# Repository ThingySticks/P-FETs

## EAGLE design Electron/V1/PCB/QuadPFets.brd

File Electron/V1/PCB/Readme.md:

FETish On A Stick
=================

Quat P Channel FETs on a Stick.

All FET's PWM-able (see notes)

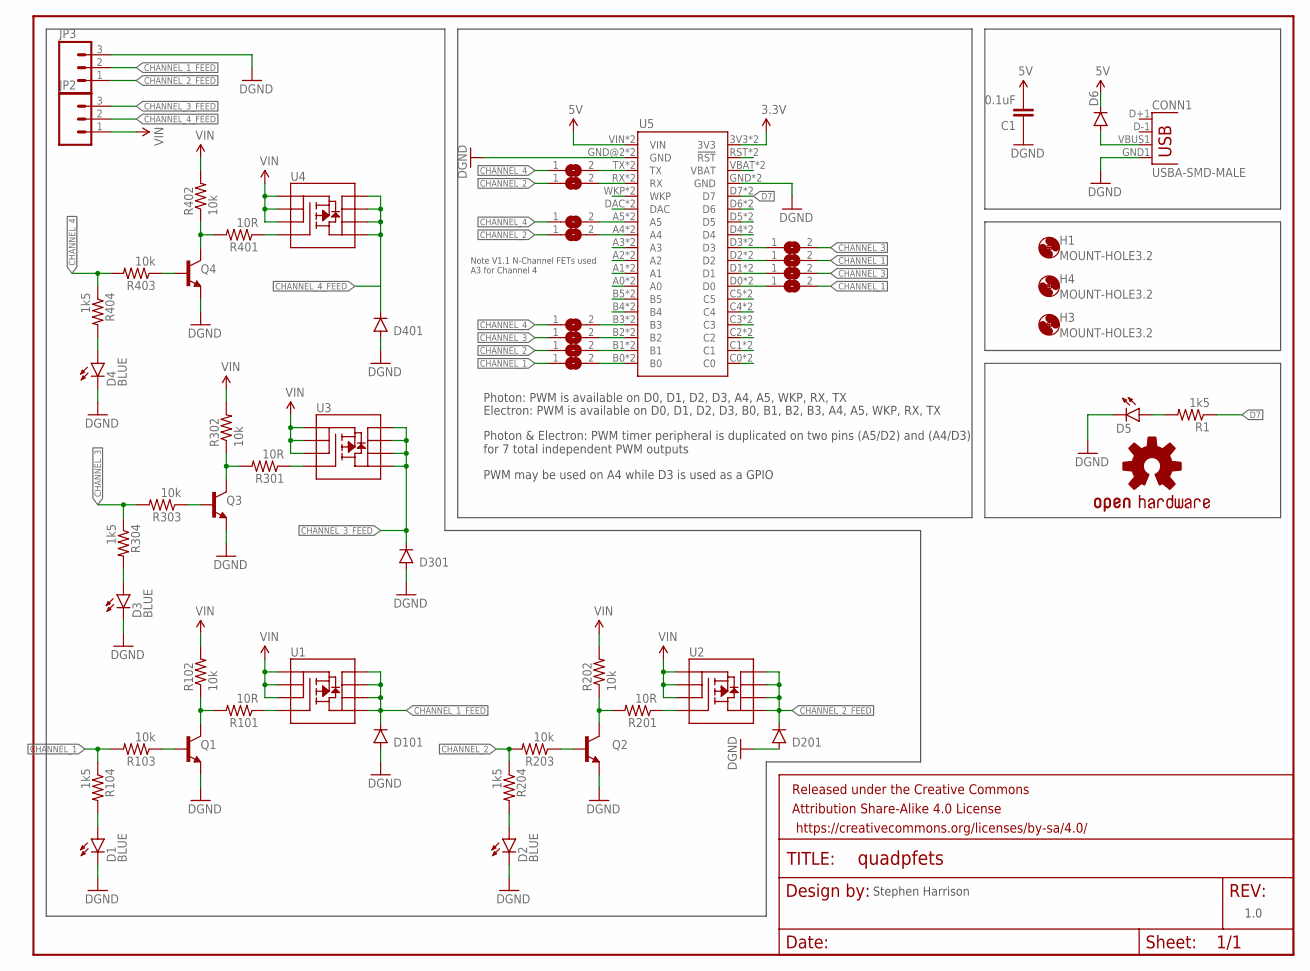
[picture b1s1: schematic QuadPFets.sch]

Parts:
C1: 0.1uF; 0805
CONN1: USBA-SMD-MALE; USB-A-SMT-MALE
D1, D2, D3, D4: BLUE; LED-1206
D5: LED1206-BOTTOM; LED-1206-BOTTOM
D6: DIODESMA; SMA-DIODE
D101, D201, D301, D401: DIODESOD123; SOD-123
FRAME2: FRAME-LETTER; CREATIVE_COMMONS
H1, H3, H4: MOUNT-HOLE3.2; 3,2
JP2, JP3: M03-SCREW-5MM; SCREWTERMINAL-5MM-3
LOGO1: OSHW-LOGOM; OSHW-LOGO-M
Q1, Q2, Q3, Q4: BC817-40SMD; SOT23-BEC
R1, R104, R204, R304, R404: 1k5; 0805
R101, R201, R301, R401: 10R; 0805
R102, R103, R202, R203, R302, R303, R402, R403: 10k; 0805
SJ1, SJ2, SJ3, SJ4, SJ5, SJ6, SJ7, SJ8, SJ9, SJ10, SJ11, SJ12: SJ
U1, U2, U3, U4: MOSFET-PCHANNEL-SOIC8SOIC8; SO08
U5: ELECTRONDUALNAMED; ELECTRON_SIMPLE_SILK_NAMES_DUAL

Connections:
3.3V: U5.3V3, U5.3V3_1 (3V3)
5V: C1.2, D6.C, U5.VIN, U5.VIN_1B (VIN)
CHANNEL_1: R103.2, R104.1, SJ4.1, SJ5.2, SJ11.2
CHANNEL_1_FEED: D101.C, JP3.2, U1.5 (D), U1.6 (D), U1.7 (D), U1.8 (D)
CHANNEL_2: R203.2, R204.1, SJ3.1, SJ8.1, SJ10.1
CHANNEL_2_FEED: D201.C, JP3.1, U2.5 (D), U2.6 (D), U2.7 (D), U2.8 (D)
CHANNEL_3: R303.2, R304.1, SJ2.1, SJ6.2, SJ12.2
CHANNEL_3_FEED: D301.C, JP2.3, U3.5 (D), U3.6 (D), U3.7 (D), U3.8 (D)
CHANNEL_4: R403.2, R404.1, SJ1.1, SJ7.1, SJ9.1
CHANNEL_4_FEED: D401.C, JP2.2, U4.5 (D), U4.6 (D), U4.7 (D), U4.8 (D)
D7: R1.1, U5.D7, U5.D7_1 (D7)
GND: C1.1, CONN1.GND1 (GND), D1.C, D2.C, D3.C, D4.C, D5.C, D101.A, D201.A, D301.A, D401.A, JP3.3, Q1.E, Q2.E, Q3.E, Q4.E, U5.GND, U5.GND@2 (GND), U5.GND_1 (GND), U5.GND_1B (GND)
unnamed: CONN1.VBUS1 (VBUS), D6.A
unnamed: Q2.C, R201.2, R202.1
unnamed: Q1.C, R101.2, R102.1
unnamed: U5.VBAT, U5.VBATT_1 (VBAT)
unnamed: U5.RST (!RST), U5.RST_1 (!RST)
unnamed: R101.1, U1.4 (G)
unnamed: D2.A, R204.2
unnamed: Q1.B, R103.1
unnamed: U5.D6, U5.D6_1 (D6)
unnamed: U5.D5, U5.D5_1 (D5)
unnamed: D5.A, R1.2
unnamed: U5.D4, U5.D4_1 (D4)
unnamed: D1.A, R104.2
unnamed: Q3.C, R301.2, R302.1
unnamed: U5.C5, U5.C5_1 (C5)
unnamed: U5.C4, U5.C4_1 (C4)
unnamed: U5.C3, U5.C3_1 (C3)
unnamed: U5.C2, U5.C2_1 (C2)
unnamed: R301.1, U3.4 (G)
unnamed: U5.C1, U5.C1_1 (C1)
unnamed: U5.C0, U5.C0_1 (C0)
unnamed: SJ8.2, U5.A4, U5.A4_1 (A4)
unnamed: SJ4.2, U5.B0, U5.B0_1 (B0)
unnamed: SJ3.2, U5.B1, U5.B1_1 (B1)
unnamed: SJ2.2, U5.B2, U5.B2_1 (B2)
unnamed: SJ1.2, U5.B3, U5.B3_1 (B3)
unnamed: U5.B4, U5.B4_1 (B4)
unnamed: U5.B5, U5.B5_1 (B5)
unnamed: U5.A0, U5.A0_1 (A0)
unnamed: U5.A1, U5.A1_1 (A1)
unnamed: U5.A2, U5.A2_1 (A2)
unnamed: U5.A3, U5.A3_1 (A3)
unnamed: SJ6.1, U5.D3, U5.D3_1 (D3)
unnamed: SJ9.2, U5.A5, U5.A5_1 (A5)
unnamed: U5.DAC, U5.DAC_1 (DAC)
unnamed: U5.WKP, U5.WKP_1 (WKP)
unnamed: SJ10.2, U5.RX, U5.RX_1 (RX)
unnamed: SJ7.2, U5.TX, U5.TX_1 (TX)
unnamed: SJ5.1, U5.D2, U5.D2_1 (D2)
unnamed: Q3.B, R303.1
unnamed: R201.1, U2.4 (G)
unnamed: D3.A, R304.2
unnamed: Q4.C, R401.2, R402.1
unnamed: R401.1, U4.4 (G)
unnamed: Q4.B, R403.1
unnamed: D4.A, R404.2
unnamed: Q2.B, R203.1
SCL: SJ12.1, U5.D1, U5.D1_1 (D1)
SDA: SJ11.1, U5.D0, U5.D0_1 (D0)
VIN: JP2.1, R102.2, R202.2, R302.2, R402.2, U1.1 (S), U1.2 (S), U1.3 (S), U2.1 (S), U2.2 (S), U2.3 (S), U3.1 (S), U3.2 (S), U3.3 (S), U4.1 (S), U4.2 (S), U4.3 (S)

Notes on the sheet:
Photon: PWM is available on D0, D1, D2, D3, A4, A5, WKP, RX, TX
Photon & Electron: PWM timer peripheral is duplicated on two pins (A5/D2) and (A4/D3) for 7 total independent PWM outputs
Electron: PWM is available on D0, D1, D2, D3, B0, B1, B2, B3, A4, A5, WKP, RX, TX
PWM may be used on A4 while D3 is used as a GPIO
1.0
Stephen Harrison
Note V1.1 N-Channel FETs used A3 for Channel 4

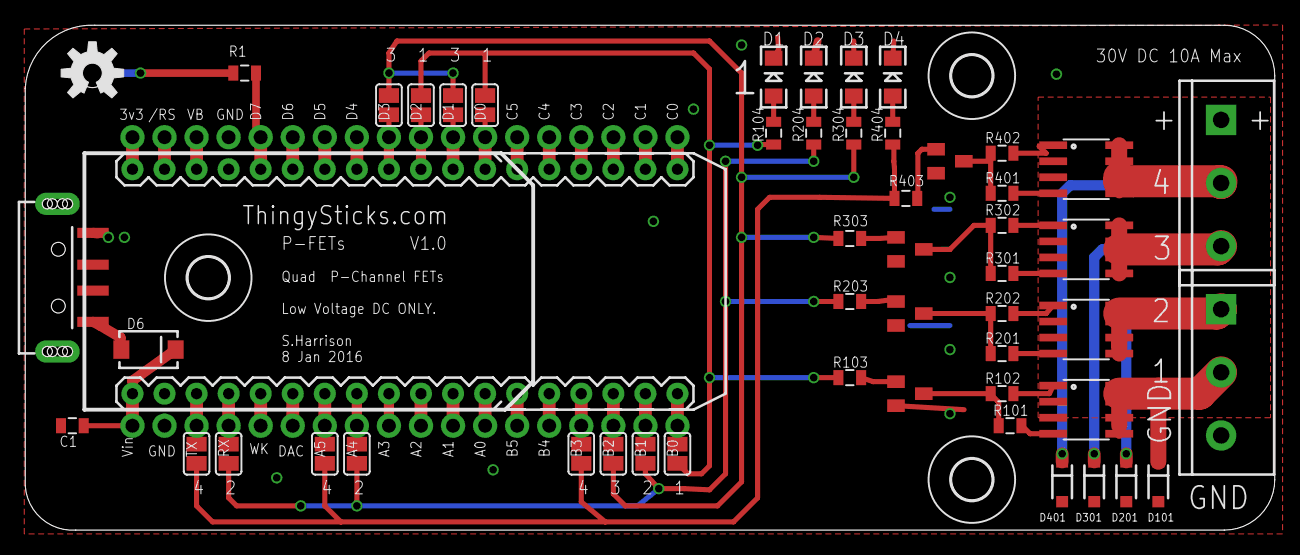
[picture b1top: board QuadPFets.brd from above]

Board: 2 copper layers, 99.0 x 40.0 mm, 57 parts (1 on the bottom side), 62 nets.

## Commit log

2017-01-09 Added datasheets and initial version of the PCB.
2017-01-09 Moved LEDs to the top of the PCB so that components can be shifted left and make space between the FETs and the terminal block so that the channel id's can be shown next to the appropriate connection.
2017-01-09 Added images and pdfs for PCB and schematic.
2017-01-09 Added images from DirtyPCBs.
    V1.0 PCBs ordered from DirtyPCBs
2017-01-09 Update to swap channel 4 onto A5 rather than A3 as A3 does not support PWM.
    DirtyPCBs order updated.
2017-01-09 Added datasheet for BC817
2017-01-09 Added more jumper options for PWM source (D0/D1 and TX/RX).
    V1.0 order updated at DirtyPCBs

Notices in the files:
parts and their libraries:
SparkFun-Connectors: Licensing: Creative Commons ShareAlike 4.0 International - https://creativecommons.org/licenses/by-sa/4.0
SparkFun-Aesthetics: Released under the Creative Commons Attribution Share-Alike 4.0 License
SparkFun-Aesthetics: https://creativecommons.org/licenses/by-sa/4.0
